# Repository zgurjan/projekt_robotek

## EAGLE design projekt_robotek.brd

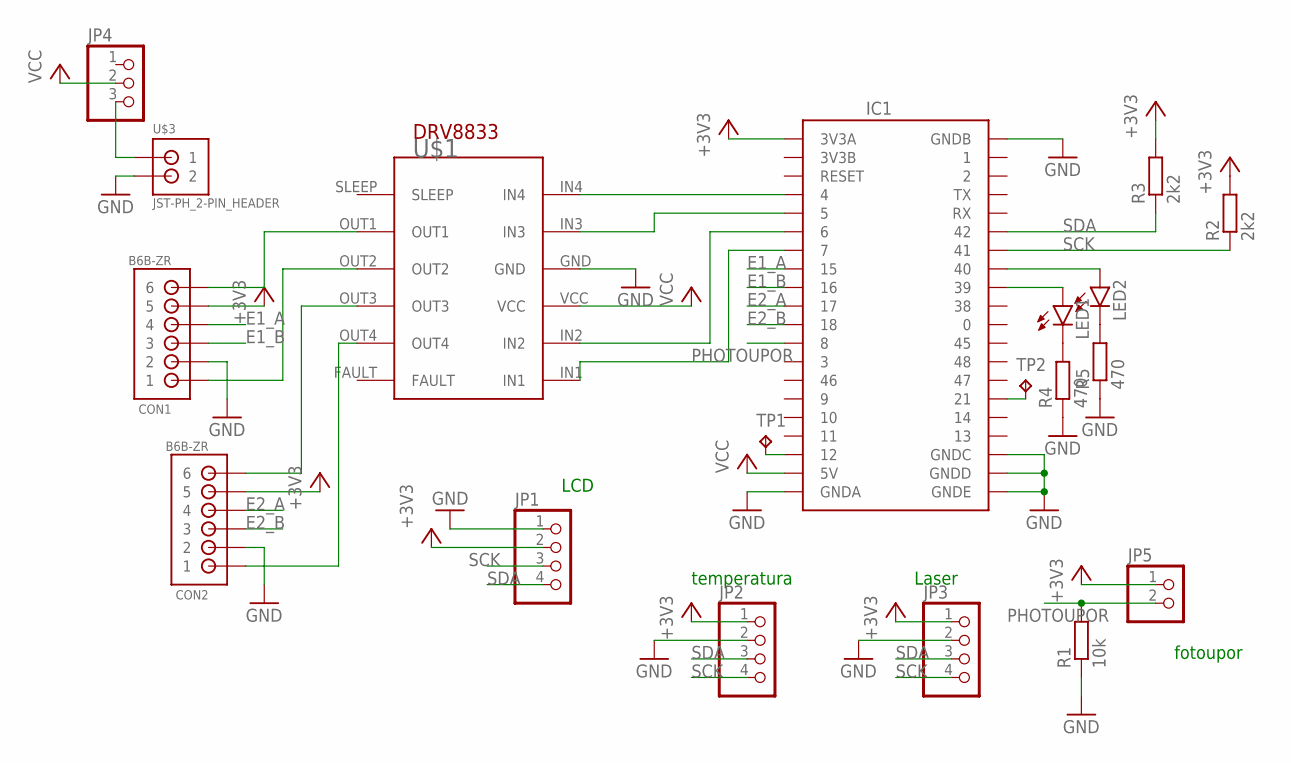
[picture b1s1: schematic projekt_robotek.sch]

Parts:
CON1, CON2: B6B-ZR
IC1: ESP32_S3; SSFD_LOLIN32_WEMOS_CHINA_W_BATT
JP1, JP2, JP3: PINHD-1X4; 1X04
JP4: PINHD-1X3; 1X03
JP5: PINHD-1X2; 1X02
LED1, LED2: LEDSML0805; SML0805
R1: 10k; R1210
R2, R3: 2k2; R0805
R4, R5: 470; R1210
TP1, TP2: TPTP20R; TP20R
U$1: POLOLU-DRV8833
U$3: JST-PH_2-PIN_HEADER; JST_B2B-PH_HEADER

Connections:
+3V3: CON1.5, CON2.5, IC1.3V3A, JP1.2, JP5.1, R2.2, R3.2
E1_A: CON1.4, IC1.15
E1_B: CON1.3, IC1.16
E2_A: CON2.4, IC1.17
E2_B: CON2.3, IC1.18
GND: CON1.2, CON2.2, IC1.GNDA4 (GNDA), IC1.GNDB, IC1.GNDC1 (GNDC), IC1.GNDD1 (GNDD), IC1.GNDE, JP1.1, JP2.2, JP3.2, R1.1, R4.1, R5.1, U$1.GND, U$3.P2 (2)
unnamed: IC1.4, U$1.IN4
unnamed: IC1.5, U$1.IN3
unnamed: IC1.6, U$1.IN2
unnamed: IC1.7, U$1.IN1
unnamed: CON1.1, U$1.OUT2
unnamed: CON1.6, U$1.OUT1
unnamed: CON2.6, U$1.OUT3
unnamed: CON2.1, U$1.OUT4
unnamed: JP4.3, U$3.P1 (1)
unnamed: LED1.C, R4.2
unnamed: JP2.1, JP3.1
unnamed: LED2.C, R5.2
unnamed: IC1.39, LED1.A
unnamed: IC1.40, LED2.A
unnamed: IC1.12, TP1.TP
unnamed: IC1.21, TP2.TP
PHOTOUPOR: IC1.8, JP5.2, R1.2
SCK: IC1.41, JP1.3, JP2.4, JP3.4, R2.1
SDA: IC1.42, JP1.4, JP2.3, JP3.3, R3.1
VCC: IC1.5V, JP4.2, U$1.VCC

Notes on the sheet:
Laser
fotoupor
temperatura
LCD

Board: 2 copper layers, 19 parts (0 on the bottom side), 26 nets, no tracks yet.

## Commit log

2022-11-17 knjižnice+skica
